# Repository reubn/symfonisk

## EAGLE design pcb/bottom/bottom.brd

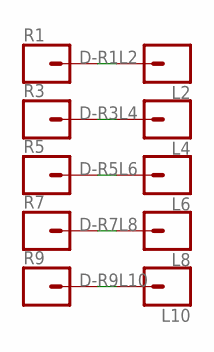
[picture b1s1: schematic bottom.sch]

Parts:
L2, L4, L6, L8, L10: CONN_01; 1X01
R1, R3, R5, R7, R9: CONN_01; 1X01

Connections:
D-R1L2: L2.1, R1.1
D-R3L4: L4.1, R3.1
D-R5L6: L6.1, R5.1
D-R7L8: L8.1, R7.1
D-R9L10: L10.1, R9.1

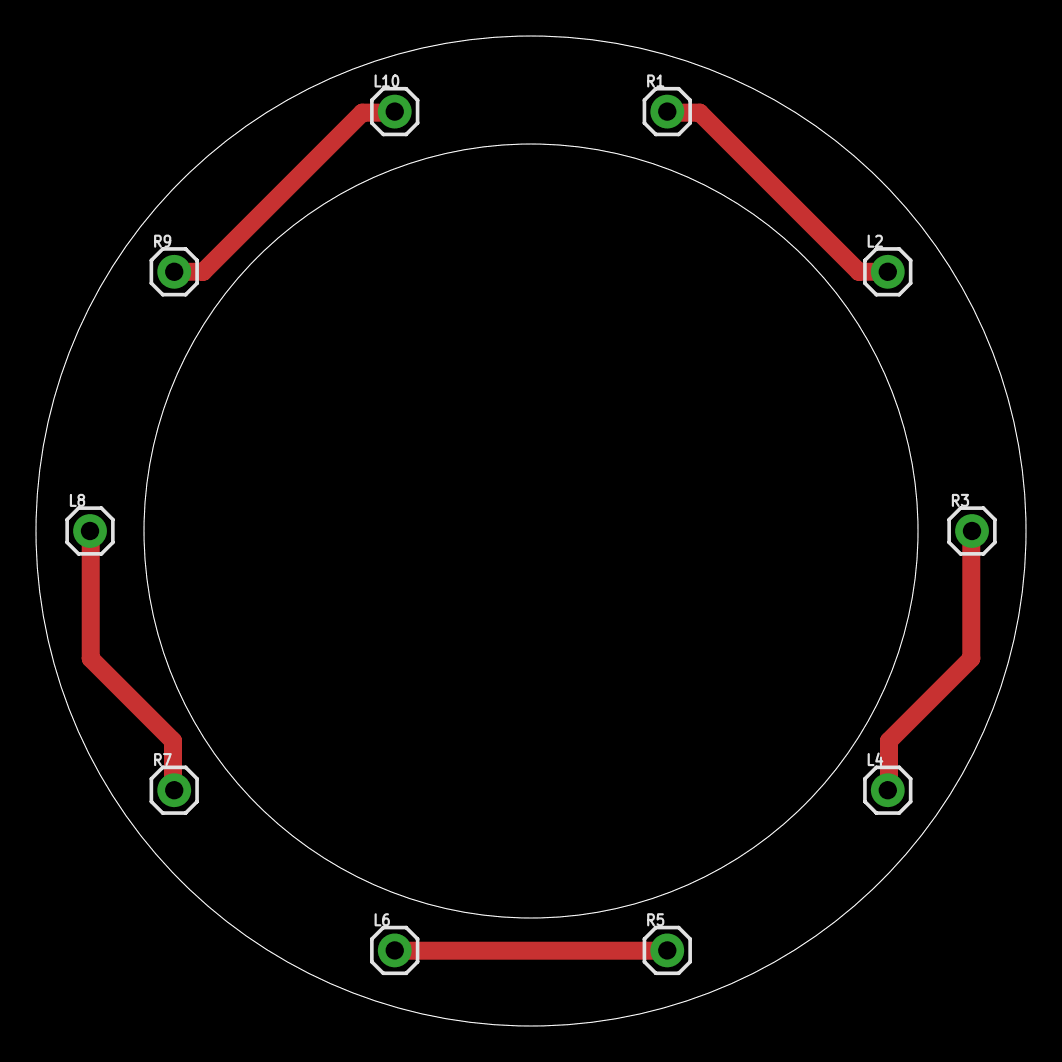
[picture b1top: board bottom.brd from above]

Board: 2 copper layers, 55.0 x 55.0 mm, 10 parts (0 on the bottom side), 5 nets.

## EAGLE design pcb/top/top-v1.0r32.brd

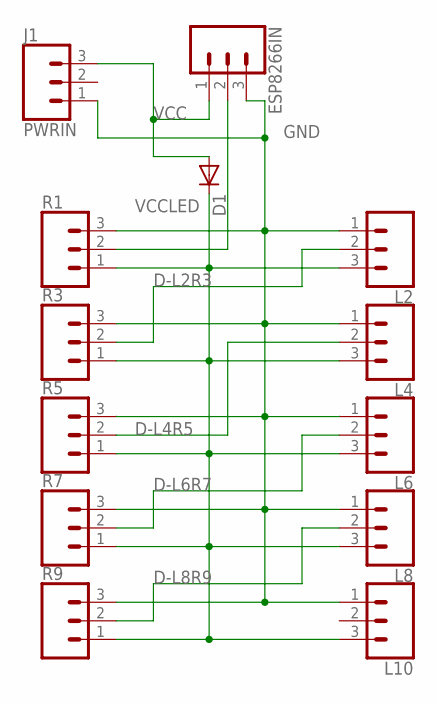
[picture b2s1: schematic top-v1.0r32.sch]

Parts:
D1: 1N4004; DO41-10
ESP8266IN: CONN_03; 1X03
J1: PWRIN; 1X03
L2, L4, L6, L8, L10: CONN_03; 1X03
R1, R3, R5, R7, R9: CONN_03; 1X03

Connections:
D-INR1: ESP8266IN.2, R1.2
D-L2R3: L2.2, R3.2
D-L4R5: L4.2, R5.2
D-L6R7: L6.2, R7.2
D-L8R9: L8.2, R9.2
GND: ESP8266IN.3, J1.1, L2.1, L4.1, L6.1, L8.1, L10.1, R1.3, R3.3, R5.3, R7.3, R9.3
VCC: D1.A, ESP8266IN.1, J1.3
VCCLED: D1.C, L2.3, L4.3, L6.3, L8.3, L10.3, R1.1, R3.1, R5.1, R7.1, R9.1

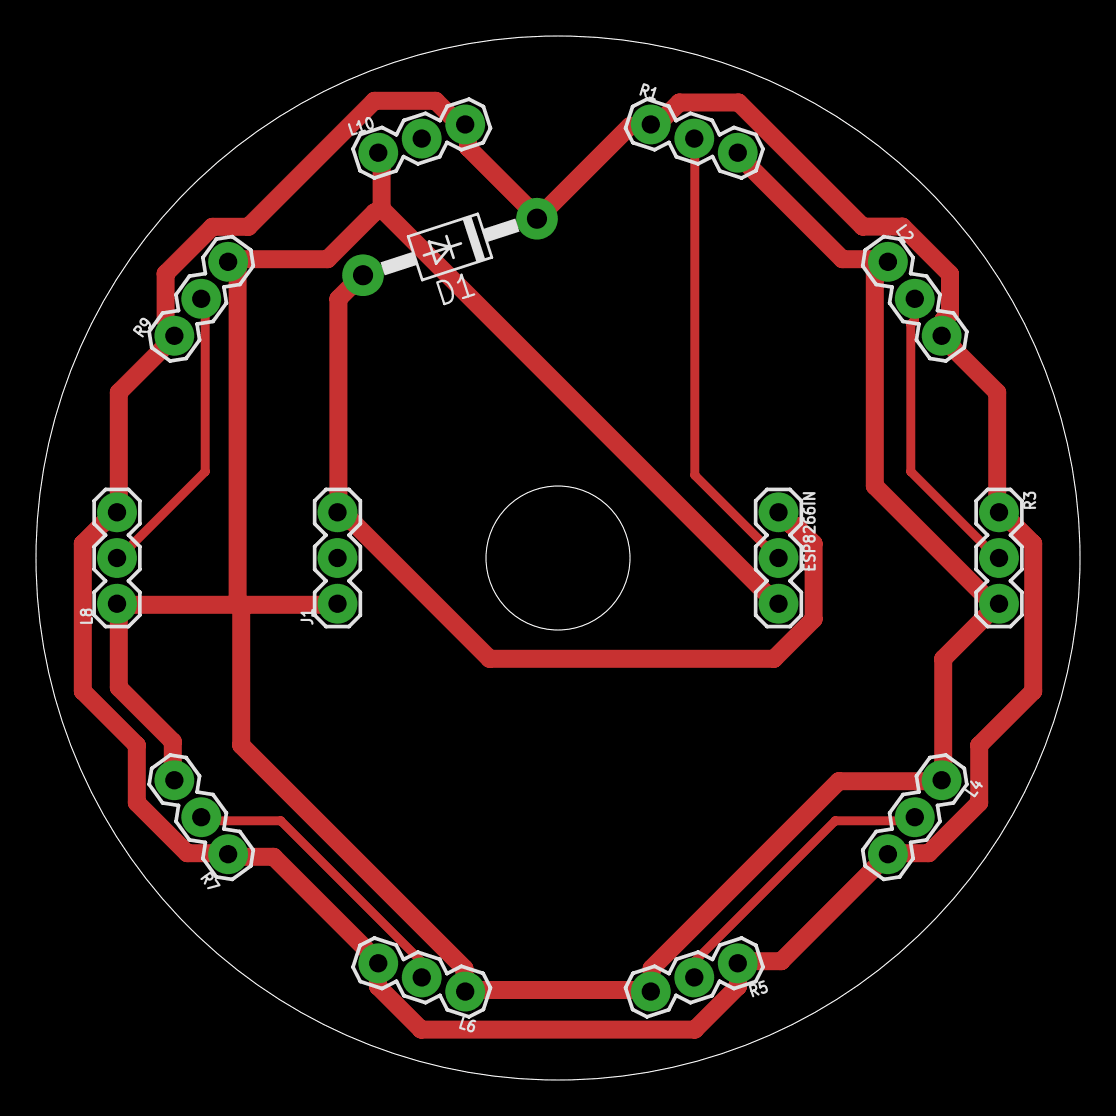
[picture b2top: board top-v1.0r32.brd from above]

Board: 1 copper layer, 58.0 x 58.0 mm, 13 parts (0 on the bottom side), 8 nets.

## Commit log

2019-12-18 First Push
2019-12-18 Remove Extra
2019-12-19 Misc
2019-12-26 Push
2020-01-06 Alexa Support
2020-05-09 🌳Better Alexa Compatibility
2020-07-12 ✨Transition to HTTP Control for HA
2021-08-29 🐛 Portal Timeout

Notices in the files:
parts and their libraries:
SparkFun-Connectors: Licensing: Creative Commons ShareAlike 4.0 International - https://creativecommons.org/licenses/by-sa/4.0
